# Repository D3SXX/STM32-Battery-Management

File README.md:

# STM32-Battery-Management Software

## List of software :

- [Quartus II 13.0sp1 Web Edition](/Software/Quartus-web-13.0.1.232-windows.tar)

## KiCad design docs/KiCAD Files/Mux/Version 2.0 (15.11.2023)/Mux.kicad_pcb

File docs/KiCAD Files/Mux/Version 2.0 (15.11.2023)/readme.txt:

Mux board version 2.0 by Vlad R.
Modified version of Mux board
Changes are -
Names for pins and connections were taken straight from the datasheet for consistency
The Schematic was simplified by using more different output socket pins
Pcb was remade from scratch to reduce the number of jumpwires (now it is 0) and to make it more easier to set up.
Also pcb design now uses only 0.8mm traces

Changes from the already made PCB -
Name is now mirrored correctly

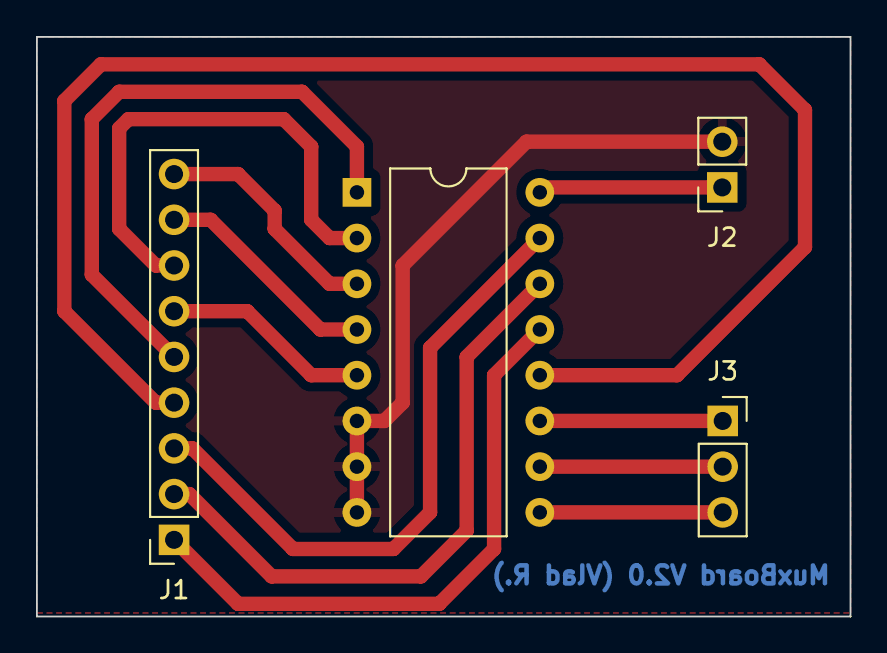
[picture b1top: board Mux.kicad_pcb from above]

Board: 2 copper layers, 45.2 x 32.2 mm, 4 parts (0 on the bottom side), 14 nets.

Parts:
J1: Conn_01x09_Pin; SOCKET_1x9
J2: Conn_01x02_Socket; SOCKET_1x2
J3: Conn_01x03_Socket; SOCKET_1x3
UR1: CD4051B; DIP-16_W10.16mm

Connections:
0: J2.2, UR1.6 (INH), UR1.7 (VEE), UR1.8 (VSS)
/A: J3.1, UR1.11 (A)
/B: J3.2, UR1.10 (B)
/C: J3.3, UR1.9 (C)
/C0: J1.1, UR1.13 (X0)
/C1: J1.2, UR1.14 (X1)
/C2: J1.3, UR1.15 (X2)
/C3: J1.4, UR1.12 (X3)
/C4: J1.5, UR1.1 (X4)
/C5: J1.6, UR1.5 (X5)
/C6: J1.7, UR1.2 (X6)
/C7: J1.8, UR1.4 (X7)
/COM OUT/IN: J1.9, UR1.3 (X)
/VDD: J2.1, UR1.16 (VDD)

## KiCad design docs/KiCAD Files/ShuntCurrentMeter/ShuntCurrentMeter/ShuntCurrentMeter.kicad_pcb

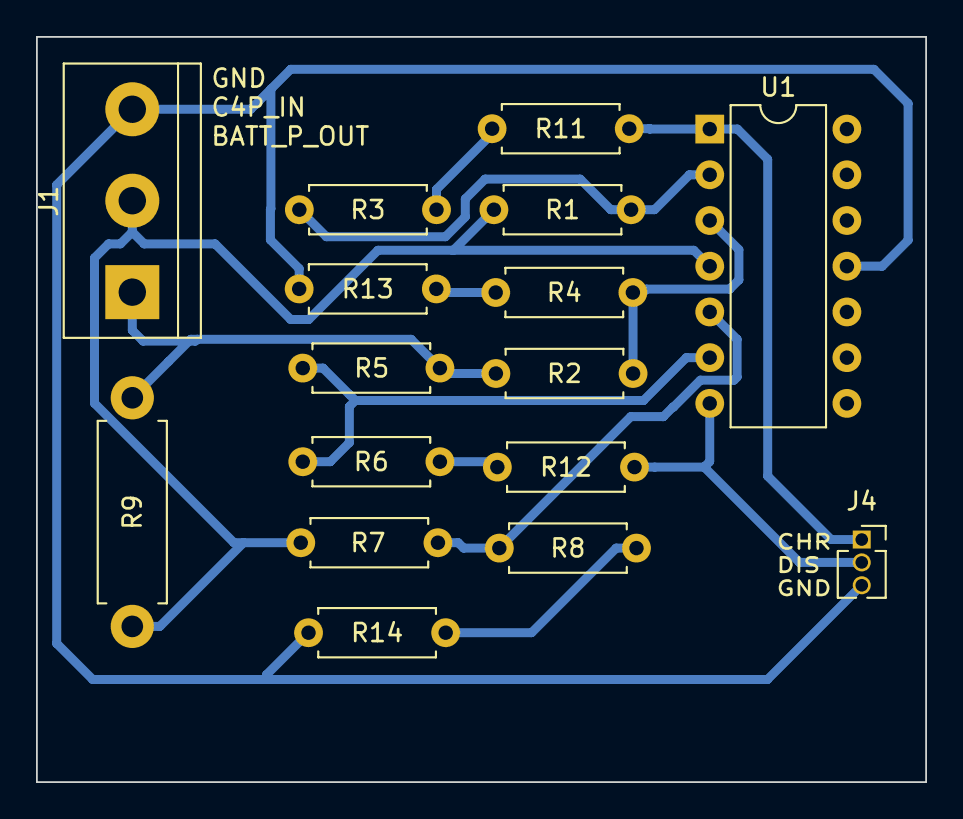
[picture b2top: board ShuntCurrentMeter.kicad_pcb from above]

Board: 2 copper layers, 49.4 x 41.4 mm, 16 parts (0 on the bottom side), 13 nets.

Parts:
J1: Screw_Terminal_01x03; TerminalBlock_bornier-3_P5.08mm
J4: Conn_01x03_Socket; PinSocket_1x03_P1.27mm_Vertical
R1, R2, R5, R7: 20K; R_Axial_DIN0207_L6.3mm_D2.5mm_P7.62mm_Horizontal
R3, R4, R6, R8: 160K; R_Axial_DIN0207_L6.3mm_D2.5mm_P7.62mm_Horizontal
R9: 0.01R; R_Axial_DIN0411_L9.9mm_D3.6mm_P12.70mm_Horizontal
R11, R12, R13, R14: 4.7K; R_Axial_DIN0207_L6.3mm_D2.5mm_P7.62mm_Horizontal
U1: LM324; DIP14

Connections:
0: J1.3, J4.3, R13.2, R14.2, U1.11 (V-)
/BATT_P_OUT: J1.1, R2.1, R5.1, R9.1
/C4_P_IN: J1.2, R1.1, R7.1, R9.2, U1.4 (V+)
/CHG: J4.1, R11.2, U1.1
/DIS: J4.2, R12.2, U1.7
unnamed: R3.2, R11.1
unnamed: R6.2, R12.1
unnamed: R4.1, R13.1
unnamed: R8.2, R14.1
unnamed: R2.2, R4.2, U1.3 (+)
unnamed: R1.2, R3.1, U1.2 (-)
unnamed: R7.2, R8.1, U1.5 (+)
unnamed: R5.2, R6.1, U1.6 (-)

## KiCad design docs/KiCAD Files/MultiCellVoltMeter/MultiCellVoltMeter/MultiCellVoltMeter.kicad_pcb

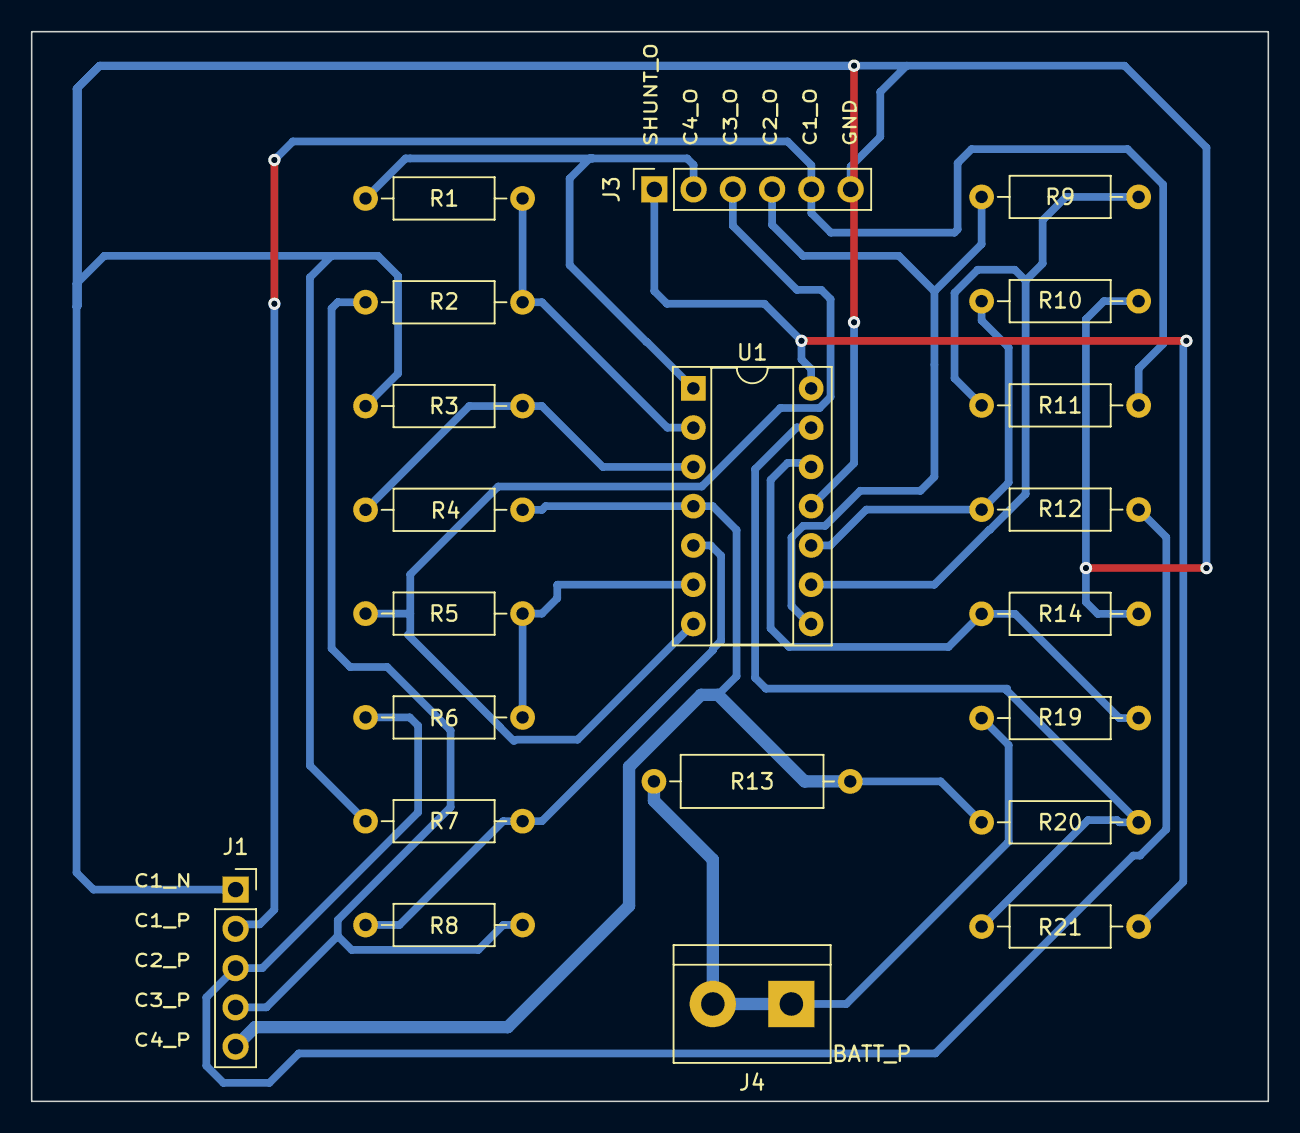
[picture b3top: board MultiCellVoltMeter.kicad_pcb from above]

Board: 2 copper layers, 80.0 x 69.2 mm, 21 parts (0 on the bottom side), 18 nets.

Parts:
J1: Conn_01x05_Socket; SOCKET_1x5
J3: Conn_01x06_Socket; SOCKET_1x6
J4: Screw_Terminal_01x02; TerminalBlock_bornier-2_P5.08mm
R1, R3, R5, R7, R9, R10: 16K; R_Axial_DIN0207_L6.3mm_D2.5mm_P10.16mm_Horizontal
R2, R4, R6, R8, R11, R12, R19, R20: 20K; R_Axial_DIN0207_L6.3mm_D2.5mm_P10.16mm_Horizontal
R13: 0.01; R_Axial_DIN0309_L9.0mm_D3.2mm_P12.70mm_Horizontal
R14, R21: 160K; R_Axial_DIN0207_L6.3mm_D2.5mm_P10.16mm_Horizontal
U1: LM324; DIP-14_W7.62mm_Socket

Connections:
0: J1.1, J3.6, R3.1, R7.1, R10.1, R14.2, U1.11 (V-)
/BATT_P_OUT: J4.1, J4.2, R13.2, R19.1
/C1_OUT: J1.2, J3.5, R11.2
/C2_OUT: J3.4, R9.1, U1.8
/C2_P: J1.3, R6.2, R12.2
/C3_OUT: J3.3, R5.1, U1.7
/C3_P: J1.4, R2.1, R8.2
/C4_OUT: J3.2, R1.2, U1.1
/C4_P: J1.5, R4.2, R13.1, R20.1, U1.4 (V+)
/SHUNT_OUT: J3.1, R21.2, U1.14
unnamed: R3.2, R4.1, U1.3 (+)
unnamed: R1.1, R2.2, U1.2 (-)
unnamed: R7.2, R8.1, U1.5 (+)
unnamed: R5.2, R6.1, U1.6 (-)
unnamed: R10.2, R12.1, U1.10 (+)
unnamed: R9.2, R11.1, U1.9 (-)
unnamed: R14.1, R19.2, U1.12 (+)
unnamed: R20.2, R21.1, U1.13 (-)

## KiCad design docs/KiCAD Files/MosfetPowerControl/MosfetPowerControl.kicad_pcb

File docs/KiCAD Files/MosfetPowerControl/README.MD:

# Mosfet Power Control

## Mosfet Basics

### Types

The **metal-oxide-semiconductor field-effect transistor** ( **MOSFET** ,  **MOS-FET** , or  **MOS FET** ) is a type of [field-effect transistor](https://en.wikipedia.org/wiki/Field-effect_transistor "Field-effect transistor") (FET), is basically a digital switche controlled by it's gate. There are normally three terminals, Drain, Source and Gate. The gate controls the current flow through D-S or S-D. There are N-Channel mosfet, P-Channel mosfet. And there enhancement type and depletion type of each.

https://en.wikipedia.org/wiki/MOSFET

### Body diode

The existance of body diode in mosfet causing the current could flow to the forward direction of the body diode, even though the gate is off.

# FDS6890A

FDS6890A is Dual N-channel mosfets in SO-8 package. With following characteristics.

## Terminology

https://woopcb.com/blog/what-is-vcc-vss-vdd-vee-in-electronics

## N-Channel Mosfets in series

N-Channel Mosfets in series offer extra control of the current due to in body diode. And puting mosfet-series-array in parrallel allow the mosfets to handle more current. In theory I_total_max = I_mosfet_max * N

Be aware, the physical diodes D1 and D2 were added only for demostration of in body diode of the N-Channel mosfet. There's no actual physical dioded added to the circuit.

The current control follows the following truth table.

| Gate 0 | Gate 1 | Current Direction | Charing | Discharging |
| ------ | ------ | ----------------- | ------- | ----------- |
| 0      | 0      | None              | NA      | NA          |
| 0      | 1      | Up to Bottom      | OFF     | ON          |
| 1      | 0      | Bottom to Up      | ON      | OFF         |
| 1      | 1      | Bidirectio        | ON      | ON          |

https://www.powerelectronictips.com/remember-mosfet-body-diode-faq/

* Pull Down Resister: 22K
* IO current limit Resister: Ceil(3.3V / 25mA * 4) = 560R

### PCB Circuit

### Simulation

## Control Logic In Practice

The maximum On state drain-source current and Off state drain-source diode forward current are 9.4A and 1.3A respectively. Therefore, we couldn't simply just allow the charging and discharging to occure without extra control.

- Start condition (0, 0)
- Discharging not allowed, charging allowed. (0, 1)
- Now the charging current ramps up --> also turn on the discharging MOSFET, say 1A. (1, 1)
- Charging drops below 1A, disable discharging MOSFET again to make sure we don't get to discharging. (0, 1)

--> keep in mind that
battery can either be charging or discharging, so if there is enough
power on the input (say solar) to power the load and charge battery,
nothing will come from the battery. If the load is higher than what
solar can provide, part of the required power comes from the battery.

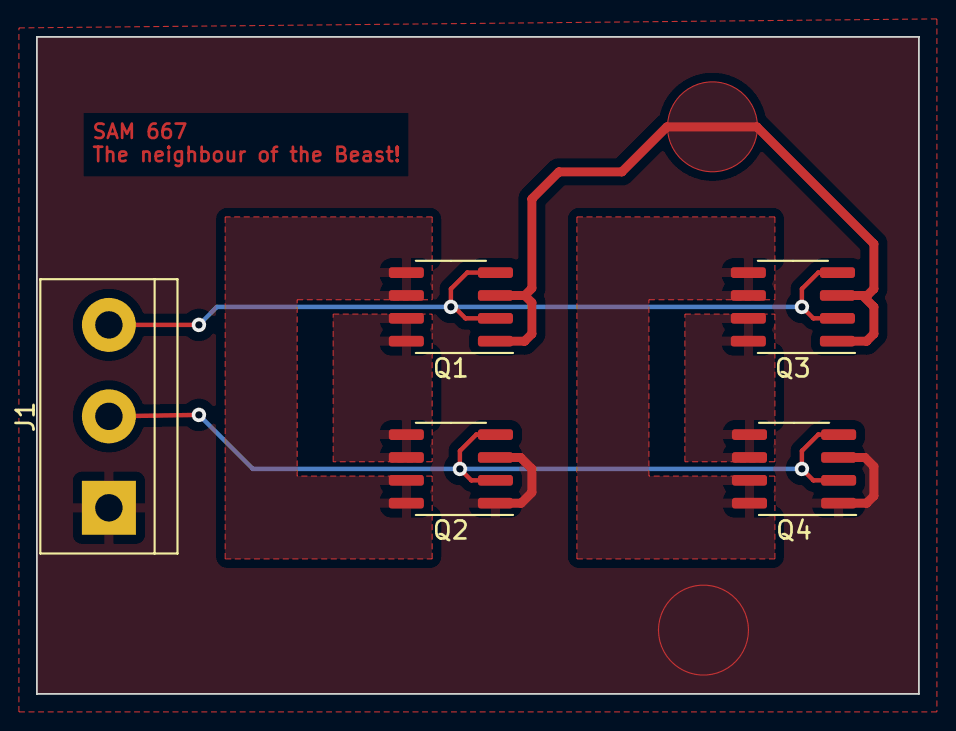
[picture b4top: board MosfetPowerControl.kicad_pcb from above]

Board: 2 copper layers, 49.0 x 36.5 mm, 5 parts (0 on the bottom side), 8 nets.

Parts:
J1: Screw_Terminal_01x03; TM_BLOCK_3P
Q1, Q2, Q3, Q4: FDS6898A; SOIC-8_3.9x4.9mm_P1.27mm

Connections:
/D1: Q1.7 (D1), Q1.8 (D1), Q2.5 (D2), Q2.6 (D2)
/D2: Q1.5 (D2), Q1.6 (D2), Q2.7 (D1), Q2.8 (D1)
/D3: Q3.7 (D1), Q3.8 (D1), Q4.5 (D2), Q4.6 (D2)
/D4: Q3.5 (D2), Q3.6 (D2), Q4.7 (D1), Q4.8 (D1)
/G1: J1.3, Q1.2 (G1), Q1.4 (G2), Q3.2 (G1), Q3.4 (G2)
/G2: J1.2, Q2.2 (G1), Q2.4 (G2), Q4.2 (G1), Q4.4 (G2)
/PSU_N: Q1.1 (S1), Q1.3 (S2), Q3.1 (S1), Q3.3 (S2)
GND: J1.1, Q2.1 (S1), Q2.3 (S2), Q4.1 (S1), Q4.3 (S2)

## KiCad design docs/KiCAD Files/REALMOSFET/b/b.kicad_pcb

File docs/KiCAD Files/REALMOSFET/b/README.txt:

IN PCB FILE
- the +5v connections may look unwired but that is because in the electrical layout  
both of the discharge and charge use +5v, so it automatically assumes they are the same thing.

- The component numbers are all over the place so there is no logic for that, change if you'd like.

-Since we are using the spider 8-pin MOSFET instead of a 3-pin MOSFET it is possible to make a connection under the component.

-It is possible to take the Q2/Q1/Q7/Q8 section and put it horizontally next to the other MOSFET section, but having an inside/outside logic for the charge/discharge is bad because it can cause noise, therefore left/right is the suggested choice.

-KICAD ALLOWS YOU TO HIGHLIGHT THE COMPONENT ON THE SCHEMA, IT WILL ALSO BE HIGHLIGHTED ON THE PCB FILE IF YOU HAVE BOTH OPEN.

-Ground is not done

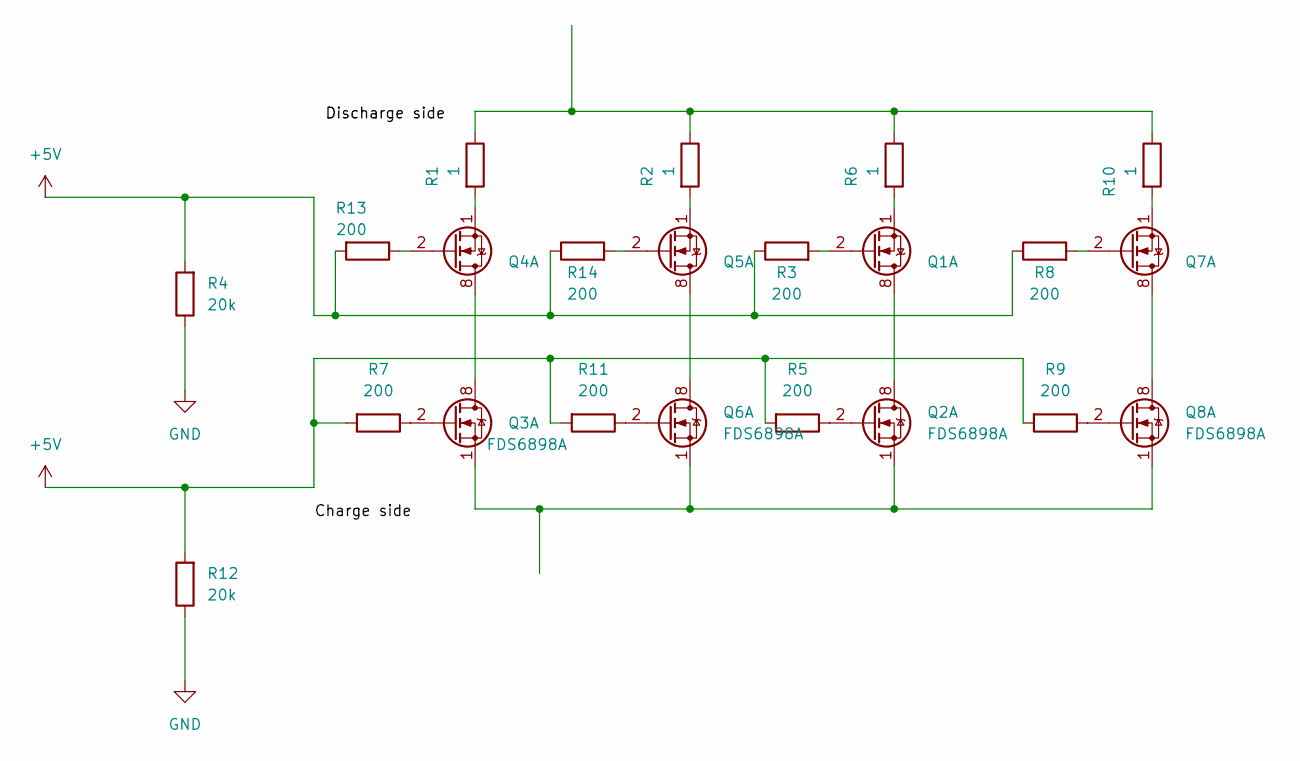
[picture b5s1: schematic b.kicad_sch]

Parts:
Q1, Q2, Q3, Q4, Q5, Q6, Q7, Q8: FDS6898A; SOIC-8_3.9x4.9mm_P1.27mm
R1, R2, R6, R10: 1; R_0603_1608Metric
R3, R5, R7, R8, R9, R11, R13, R14: 200; R_0603_1608Metric
R4, R12: 20k; R_0603_1608Metric

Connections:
+5V: R3.1, R4.2, R5.2, R7.2, R8.1, R9.2, R11.2, R12.2, R13.2, R14.1
GND: R4.1, R12.1
unnamed: Q1.7 (D1), Q1.8 (D1), Q2.7 (D1), Q2.8 (D1)
unnamed: Q1.2 (G1), R3.2
unnamed: Q1.1 (S1), R6.2
unnamed: Q2.2 (G1), R5.1
unnamed: Q2.1 (S1), Q3.1 (S1), Q6.1 (S1), Q8.1 (S1)
unnamed: Q3.7 (D1), Q3.8 (D1), Q4.7 (D1), Q4.8 (D1)
unnamed: Q3.2 (G1), R7.1
unnamed: Q4.2 (G1), R13.1
unnamed: Q4.1 (S1), R1.2
unnamed: Q5.7 (D1), Q5.8 (D1), Q6.7 (D1), Q6.8 (D1)
unnamed: Q5.2 (G1), R14.2
unnamed: Q5.1 (S1), R2.2
unnamed: Q6.2 (G1), R11.1
unnamed: Q7.7 (D1), Q7.8 (D1), Q8.7 (D1), Q8.8 (D1)
unnamed: Q7.2 (G1), R8.2
unnamed: Q7.1 (S1), R10.2
unnamed: Q8.2 (G1), R9.1
unnamed: R1.1, R2.1, R6.1, R10.1

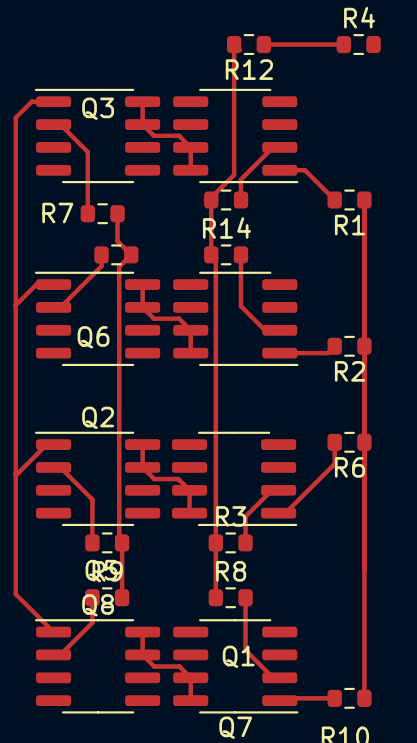
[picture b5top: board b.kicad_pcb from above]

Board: 2 copper layers, 22 parts (0 on the bottom side), 20 nets.

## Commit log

2023-09-08 added branching model
2023-09-08 added atollic-truestudio-pipeline
2023-09-08 added naming convention and clang-format
2023-09-08 Update README.md
    Added TODO list + future prospects
2023-09-08 Add logs and project information
2023-09-11 Add documentation
2023-09-11 Revert README.md
2023-09-18 add files
2023-09-18 trying out LL functions
2023-09-18 Rewrote ADC Temp Reader only with LL functions
2023-09-18 Add files via upload
    Extremely useful reference manual for LL
2023-09-18 Update repo
2023-09-21 Add serial read script
2023-09-21 Add python script for SQlite and example database
2023-09-24 Add lm35-LL-v2
2023-09-25 Add documentation and update project-information
2023-09-25 Created ReadMux func
2023-09-25 Update mux code
2023-09-29 Update main.c
    Make a delay after mux channel switch
    Add temp
    Improve comments
2023-09-29 Added KiCAD schemas
2023-10-02 modbus initial commnit
2023-10-02 IoT-ticket init commit
2023-10-04 read from stm32 via modbus was added
2023-10-04 modbus tunning
2023-10-04 MosfetPowerControl and MultiCellBatteryMeter
2023-10-05 README added
2023-10-09 Better circuit design for MPC
2023-10-09 Better circuit design for MCB
2023-10-09 Better MPC sim circuit
2023-10-09 better error handling for wrong size modbus frame
2023-10-09 better error handling
2023-10-12 Add pcb design and update documentation
2023-10-12 Add new logs
2023-10-12 Add logs for 12.10.2023
2023-10-24 MosfetPowerControl PCB and Simu
2023-10-24 add backup to ignorelist
2023-10-24 ignore backups
2023-10-25 gitignore
2023-10-25 move modbus_routine out from interrupt to main
2023-10-25 better documentation
2023-10-26 Negative temperature meas. and ADC optimization
2023-10-26 Update code
2023-10-26 add logs for 25.10.2023
2023-10-26 dma transmission error handling Too long/Too shrot
2023-10-26 better src code placement
2023-10-26 Added timer2
2023-10-26 added adc
2023-10-27 better documentation for lib timer
2023-10-27 better directory structure
2023-10-27 better systick_init and delay_ms
2023-10-27 configure moc_adc_read by now
2023-10-27 better modbus function_4 logic
2023-10-27 better atomic protection
2023-10-27 added random delay for testing
2023-10-27 moved SysTick_init(), disabled some debugging code
2023-10-27 read all data from modbus now
2023-11-08 new structure for testing
2023-11-08 Update Actions & Improve compatibility with linux
2023-11-09 set up embedded_test and native_test
2023-11-09 modbus test cases
2023-11-10 better debug control
2023-11-10 moved [env:nucleo_l152re] as default project
2023-11-10 refactored for easier calling and testing
2023-11-10 better error report
2023-11-10 reply data len fix
2023-11-10 better debug and format
2023-11-10 explicitly set test speed and port.
2023-11-10 modified modbus test
2023-11-10 removed unneeded delay
2023-11-10 Multiplexer Schema and PCB
2023-11-10 mosfet libs
2023-11-10 current meter schema
2023-11-10 lm324 lib and ngspice quad model
2023-11-10 current meter pcb
2023-11-10 multi cell meter schema + pcb
2023-11-10 added ignore rules
2023-11-10 Fixed file and header names
2023-11-10 Added comments and modified vscode config
2023-11-10 Create initial files for ADC unit test
2023-11-10 Update unit test code
2023-11-10 Added ADC tests
2023-11-10 Added more test functions
2023-11-10 Fix test_adc - find_median:Fail
2023-11-11 add logs for 08.11.2023
2023-11-11 Rename report-08.10.2023.txt to report-08.11.2023.txt
2023-11-13 added adc library
2023-11-13 added mux library
2023-11-13 modified moc_adc library
2023-11-13 updated main for new adc related functions
2023-11-13 fixed function pointer declaration syntax.
2023-11-13 fixed MUX_SEL_CHx definition
2023-11-13 added function declarations for subroutines: read_current_routine(), read_temperature_routine(), read_cell_voltage_routine()
2023-11-13 fixed led indicator
2023-11-13 added test_adc
2023-11-13 better testing data for temperature
2023-11-13 added extra helper macros
2023-11-13 fixed current and temperature convertion bugs
2023-11-13 better moc_adc functions
2023-11-13 removed delay_ms for less dependencies.
2023-11-13 configs update
2023-11-13 updated current routine
2023-11-14 test_mux added
2023-11-14 enable HSI for ADC
2023-11-14 better comments
2023-11-14 bug fix on MUX
2023-11-14 return logic fix
2023-11-14 proper reset mux pins
2023-11-14 intellisense update
2023-11-15 created test_adc in native environment
2023-11-15 refactored adc for better testing
2023-11-15 dependency fix
2023-11-15 config updates
2023-11-15 added preprocessor guard
2023-11-15 moved to new directory
2023-11-15 renamed for solving conflicts in Windows
2023-11-15 Added Print Output
2023-11-15 better test_mux
2023-11-15 fixed dependency according to new libadc
2023-11-15 modified libmux for much clearer definitions.
2023-11-15 added waiting logic for mux_set and reset
2023-11-15 added test_mostfet_control
2023-11-15 TDD, libmosfet failed test, Not Implemented.
2023-11-15 added libmosfet_control
2023-11-15 dependency updates
2023-11-15 test_mosfet_control ready and passed
2023-11-15 added MAPPING documentation
2023-11-15 Add new MUX Board & Datasheet
2023-11-15 test_batter_manager_voltage_check() ready
2023-11-15 added battery control routine
2023-11-15 added libbattery_manager
2023-11-15 added more prototypes
2023-11-15 added temperature test
2023-11-15 dependency update
2023-11-16 Batter comments
2023-11-16 added temp check, status set/reset/get/overwrite.
2023-11-16 fixed a typo
2023-11-16 temperature check ready
2023-11-16 better defines
2023-11-16 TDD, should failed current test.
2023-11-16 added current_check()
2023-11-16 added current discharge test
2023-11-21 Add Mux board v2.1
2023-11-21 Battery Manger ready
2023-11-21 test battery manager ready
2023-11-21 changed truth table
2023-11-21 \r\n for windows support
2023-11-21 better naming for the gates
2023-11-21 replaced battery control with battery_manager
2023-11-21 configed for latest built
2023-11-21 modified discharging current test
2023-11-23 - Data for lm35 now is collected using A1 and A2 instead of using mux - Cleaned code (removed unused variables, old comments) - Added support for A2 input - Fixed a bug in find_median() (out of bound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
2023-11-23 add logs for 23.11.2023
2023-11-24 decoupled adc_read from adc_convert
2023-11-24 temp sensor using dedicated adc pins now
2023-11-24 DATA AND PIN MAPPING UPDATE
2023-11-24 better debug message
2023-11-24 updated test_adc for new decoupled adc functions
2023-11-24 fixed charging and discharging
2023-11-24 new temperature routine logic
2023-11-24 build_flags update
2023-11-24 fixed comments
2023-11-24 batter type converting
2023-11-24 Fixed A2 pin input Fixed USART output for Mux Added decimal point for temperature measurement Removed useless Temp calculations from mux USART output Limited channels to 4
2023-11-28 new temperature_check logic
2023-11-28 adc settings
2023-11-28 Enabled PA1 PA4 for Temp Sensor inputs
2023-11-28 port update
2023-11-28 updated main routine order
2023-11-28 Updated docments
2023-11-28 added project directory map
2023-11-28 modified temperature check
2023-12-01 Added Mosfet control logic Added battery states
